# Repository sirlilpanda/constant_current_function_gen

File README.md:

# kicad project constant_current_function_gen

a cool table showing the workflow of all the kicad projects.
| project_name | DRC | ERC |
| ------------ | --- | --- |
| current_gen_class_ab | [❌](https://github.com/sirlilpanda/constant_current_function_gen/actions/runs/16821990167/attempts/1#summary-47650711295)| [❌](https://github.com/sirlilpanda/constant_current_function_gen/actions/runs/16821990167/attempts/1#summary-47650711311) | 
| current_gen | [✅](https://github.com/sirlilpanda/constant_current_function_gen/actions/runs/16821990167/attempts/1#summary-47650711297)| [✅](https://github.com/sirlilpanda/constant_current_function_gen/actions/runs/16821990167/attempts/1#summary-47650711362) | 

for a quick guide check [project setup](#project-setup)

This is a simple project template for new kicad projects. This template has some basic setup already completed such as workflows for auto creating all the things you forget when creating a kicad project such as:

| project_name | schematic | bom | bom report | gerbers |
| ------------ | --------- | --- | ---------- | ------- |
| [current_gen_class_ab](https://github.com/sirlilpanda/constant_current_function_gen/tree/main/./Hardware/current_gen_class_ab) | [current_gen_class_ab_schematic.pdf](https://github.com/sirlilpanda/constant_current_function_gen/tree/main/current_gen_class_ab_schematic.pdf) | [current_gen_class_ab_bill_of_materials.csv](https://github.com/sirlilpanda/constant_current_function_gen/tree/main/current_gen_class_ab_bill_of_materials.csv) | [current_gen_class_ab_bom_report.md](https://github.com/sirlilpanda/constant_current_function_gen/tree/main/current_gen_class_ab_bom_report.md) | [current_gen_class_ab_grbr.zip](https://github.com/sirlilpanda/constant_current_function_gen/tree/main/current_gen_class_ab_gerber.zip) |
| [current_gen](https://github.com/sirlilpanda/constant_current_function_gen/tree/main/./Hardware/current_gen) | [current_gen_schematic.pdf](https://github.com/sirlilpanda/constant_current_function_gen/tree/main/current_gen_schematic.pdf) | [current_gen_bill_of_materials.csv](https://github.com/sirlilpanda/constant_current_function_gen/tree/main/current_gen_bill_of_materials.csv) | [current_gen_bom_report.md](https://github.com/sirlilpanda/constant_current_function_gen/tree/main/current_gen_bom_report.md) | [current_gen_grbr.zip](https://github.com/sirlilpanda/constant_current_function_gen/tree/main/current_gen_gerber.zip) |

This workflow will also run the design rules check on the PCB and schematic to ensure that you upload a working PCB. These reports are uploaded as summaries within the github [actions tab](https://github.com/sirlilpanda/constant_current_function_gen/actions/runs/16821990167). This template has a simple schematic PCB in it (because DRC fails on an empty PCB). Shown below is the example PCB.

besides from that the project also has:

- common predefined trace widths
- smallest vias size [JLCPBC allows](https://jlcpcb.com/capabilities/Capabilities#Drilling)
- custom net colours in the schematic editor
    - `red` for +V
    - `blue` for -V
    - `grey` for ground

to create a repo from this template follow this [guide](https://docs.github.com/en/repositories/creating-and-managing-repositories/creating-a-repository-from-a-template)

contained in this template are:
---
- `.github/` : all files relating to github actions and other admin see [here](https://docs.github.com/en/communities/setting-up-your-project-for-healthy-contributions) for more example of what can be placed in it
    - `report_processing` : where the python scripts are stored for processing the json report data from kicad
    - `report_templates` : where the template for said reports are stored
    - `workflows/` : this is where the github actions are kept
        - `main.yaml` : the main github action that will auto generate all files required and run DRC and ERC
    - `rename.py` : the script for renaming the project
- `hardware/` : this is where the kicad projects live note this can be changed
- `docs/` : this is where the generate docs are placed by default
    - `BOM/`     : where the bill of materials and price breakdown are kept
        - `bill_of_materials.csv`: the auto generated bom for the kicad project
        - `bom_report.md` : a report for the bill of materials
    - `template_schematic.pdf` : the schematic for the kicad project, auto generated by the github action
- `pcbs/` : this is where the auto generated gerbers for the kicad project are stored

- `res/` : where resources are stored for the README

- `.gitignore`: a slightly modified gitignore from the [standard one](https://github.com/github/gitignore/blob/main/KiCad.gitignore)

- `project_settings.yaml` : where the settings for this project is stored

- `README.md` : this file, suggest you change this one creating your project

## project settings
there are currently very few project settings that can be changed (will will be change in the future) these are:
| setting                     | description                                                       |
| --------------------------- | ----------------------------------------------------------------- |
| has_been_set_up             | a flag to tell the setup action if the project has been set up    |
| project_name                | the name of the project, this will be set to the name of the repo |
| production_formats          | the output production format for the PCBs                         |
| dynamic_read_me             | allow the readme to be updated using the given template           |
| bom_template_path           | the template used to write the bom report files                   |
| erc_report_template_path    | the template used to write the erc report files                   |
| drc_report_template_path    | the template used to write the drc report files                   |
| readme_template_path        | the template used to write projects readme                        |
| schematic_output_name       | the name suffix of the generated schematics                       |
| bom_csv_output_name         | the name suffix of the generated bom csv file                     |
| bom_report_output_name      | the name suffix of the generated bom report                       |
| production_file_output_name | the name suffix of the generated production file                  |
| schematic_output_path       | the output path of the generated schematics files                 |
| bom_csv_output_path         | the output path of the generated bom csv file                     |
| bom_report_output_path      | the output path of the generated bom report                       |
| production_file_output_path | the output path of the generated production file                  |

## project setup

### creating a new repo with the template

creating a new template from a repo is simple:

1. click on the button in the top right hand corner called `use this template`

2. when the drop down menu appears click on `create a new repository`

3. once you click you will be brought to this page, note that the repo name you choose here will be the name that you kicad project is called.

after these steps you then need to configure the repo settings to do their magic see [configuring repo settings](#configuring-repo-settings) for what to do next.

### configuring repo settings

once you have created a new repo with the template, you ill have to configure the github action settings. this is because you will get an error that looks something along these lines:

where the action can not commit the changes due to not having permissions follow these steps:
1. open the repo setting

2. then head in to actions : General

3. then scroll down to workflow permissions and ensure that both
    `Read and write permissions` and `Allow GitHub Actions to create and approve pull requests` are ticked as seen below

this should fix the problem if not, go harass stack overflow they need it
Once all of these steps have been followed the workflow should be passing, however the `README.md` will only update on the next push request.

## editing the readme

As this repo can and will automatically update the repo corresponding to the given readme template. If you dont want to use this you can always disable this by setting the `dynamic_read_me` to `false`. but if you want some very cool features like auto updating tables to show what projects are passing the rules check or simple links to parts of your directory. then have a look at the template readme and learn [mustache](https://mustache.github.io/)

## improvements

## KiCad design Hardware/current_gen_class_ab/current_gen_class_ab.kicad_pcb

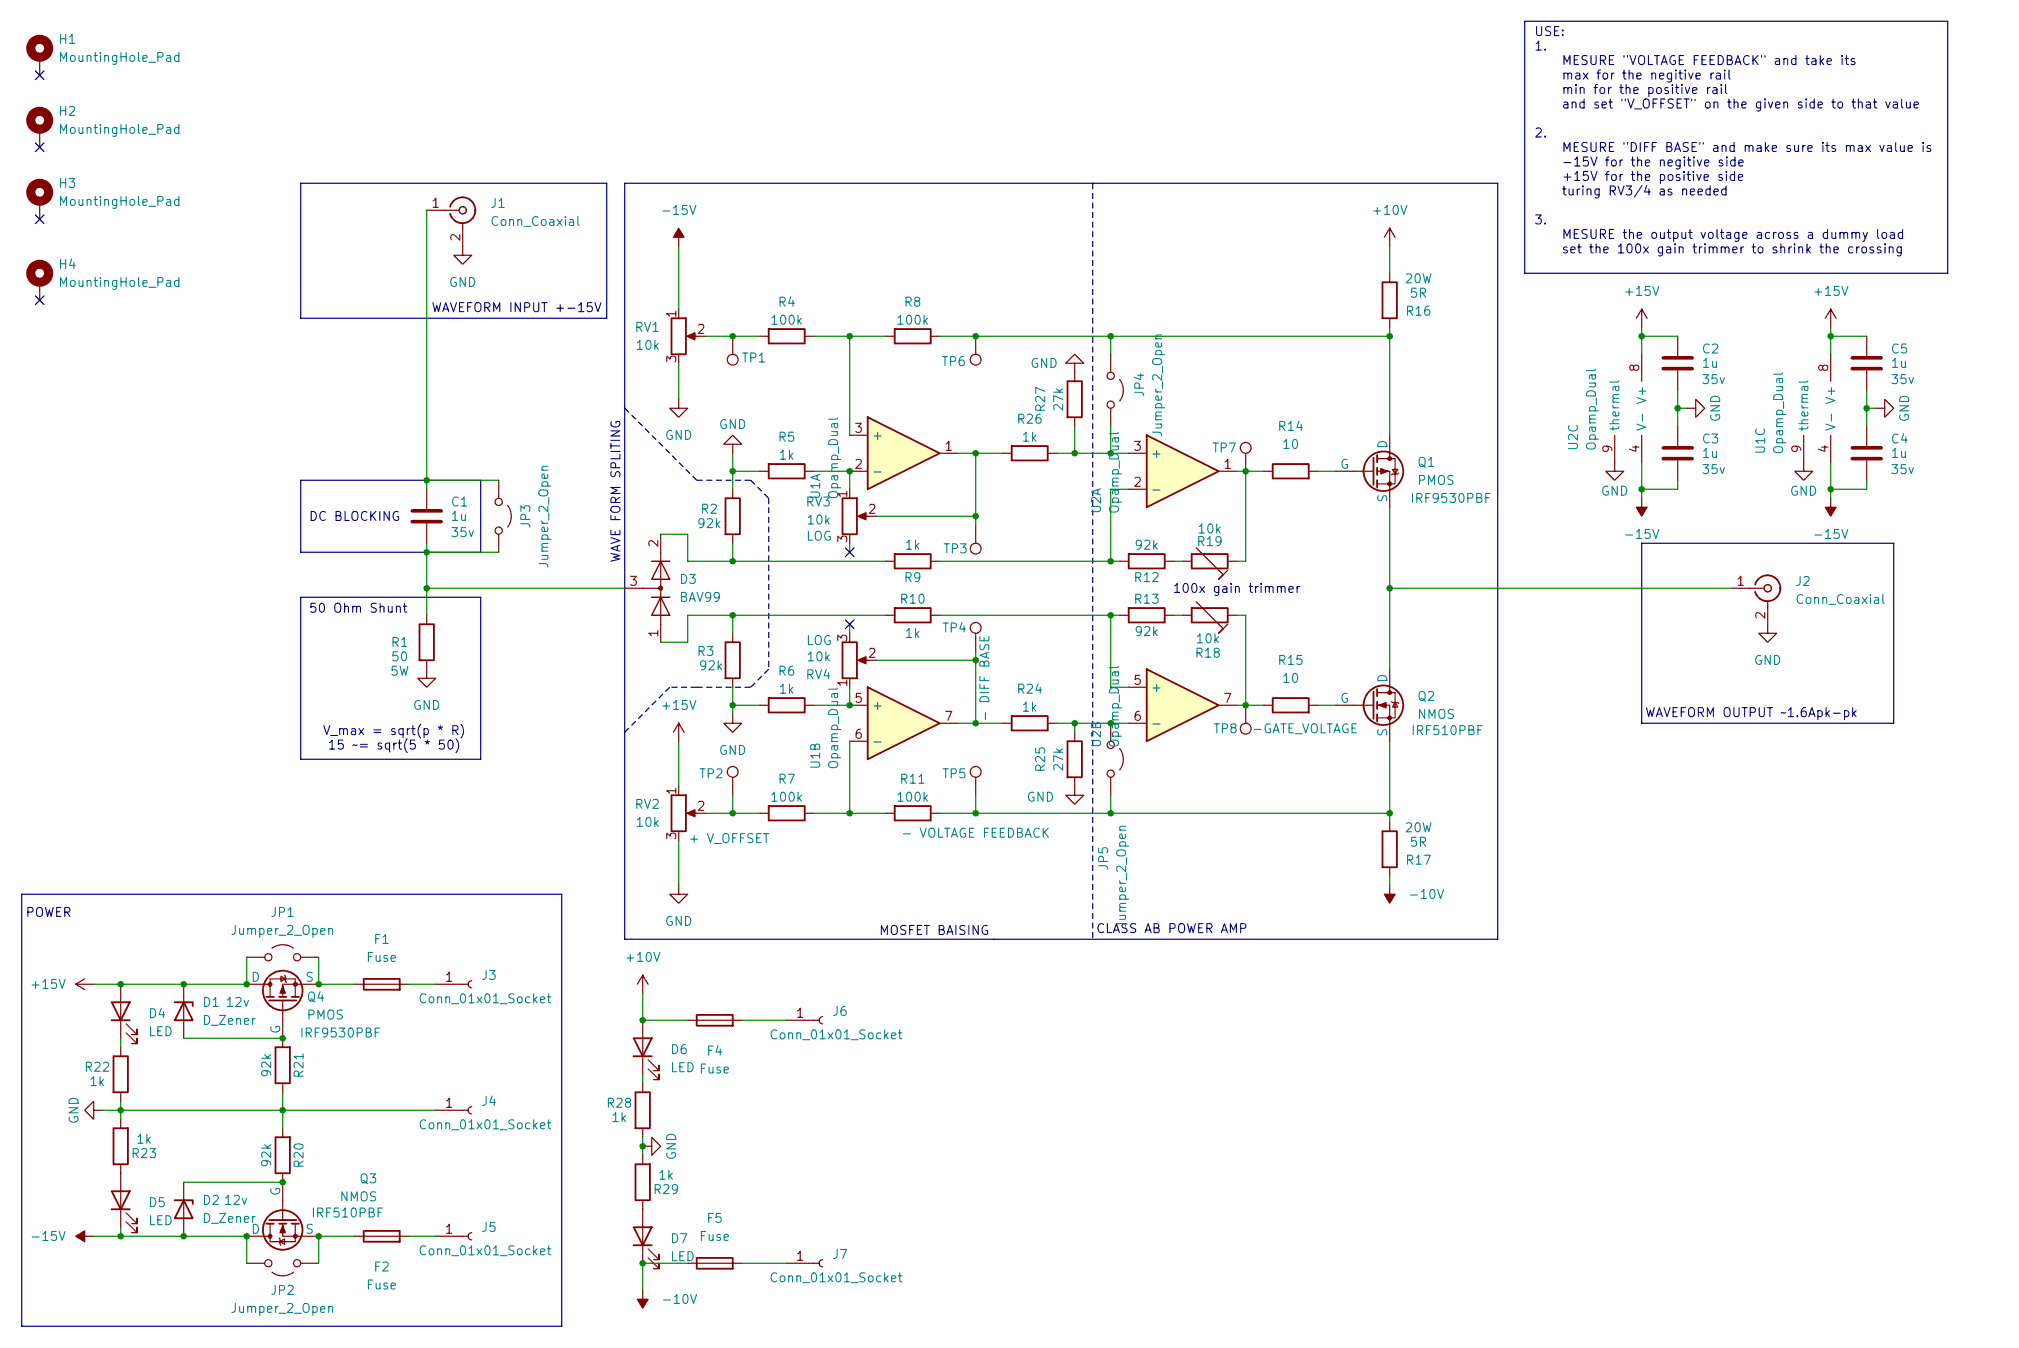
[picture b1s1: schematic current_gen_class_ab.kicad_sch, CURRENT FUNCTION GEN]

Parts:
C1, C2, C3, C4, C5: 1u; C_0805_2012Metric
D1, D2: D_Zener; D_SOD-123
D3: BAV99; SOT-23; Manufactor Part Number BAV99
D4, D5, D6, D7: LED; D_0603_1608Metric
F1, F2, F4, F5: Fuse; Fuseholder_Clip-5x20mm_Bel_FC-203-22_Lateral_P17.80x5.00mm_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
H1, H2, H3, H4: MountingHole_Pad; MountingHole_3.2mm_M3_DIN965_Pad
J1, J2: Conn_Coaxial; BNC_TEConnectivity_1478035_Horizontal
J3, J4, J5, J6, J7: Conn_01x01_Socket; Banana_Jack_1Pin
JP1, JP2, JP3, JP4, JP5: Jumper_2_Open; SolderJumper-2_P1.3mm_Open_TrianglePad1.0x1.5mm
Q1, Q4: PMOS; TO-220-3_Horizontal_TabDown
Q2, Q3: NMOS; TO-220-3_Horizontal_TabDown
R1: 50; R_Axial_DIN0309_L9.0mm_D3.2mm_P12.70mm_Horizontal
R2, R3, R12, R13, R20, R21: 92k; R_0603_1608Metric
R4, R7, R8, R11: 100k; R_0603_1608Metric
R5, R6, R9, R10, R22, R23, R24, R26, R28, R29: 1k; R_0603_1608Metric
R14, R15: 10; R_0603_1608Metric
R16, R17: 5R; TO-220-2_Horizontal_TabDown
R18, R19: 10k; Potentiometer_Bourns_3296W_Vertical
R25, R27: 27k; R_0603_1608Metric
RV1, RV2: 10k; POT_P120PK-x25_TTE
RV3, RV4: 10k; Potentiometer_Bourns_PTV09A-1_Single_Vertical
TP1, TP2, TP3, TP4, TP5, TP6, TP7, TP8: TestPoint; TestPoint_Bridge_Pitch2.54mm_Drill1.3mm
U1, U2: Opamp_Dual; SOIC-8-1EP_3.9x4.9mm_P1.27mm_EP2.29x3mm_ThermalVias

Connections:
+10V: D6.2 (A), F4.1, R16.1
+15V: C2.2, C5.2, D1.1 (K), D4.2 (A), JP1.1 (A), Q4.1 (D), RV2.1, U1.8 (V+), U2.8 (V+)
-10V: D7.1 (K), F5.1, R17.2
-15V: C3.1, C4.1, D2.2 (A), D5.1 (K), JP2.2 (B), Q3.1 (D), RV1.1, U1.4 (V-), U2.4 (V-)
GND: C2.1, C3.2, C4.2, C5.1, J1.2 (Ext), J2.2 (Ext), J4.1, R1.2, R2.1, R3.2, R5.2, R6.2, R20.2, R21.1, R22.2, R23.2, R25.2, R27.1, R28.2, R29.2, RV1.3, RV2.3, U1.9 (thermal), U2.9 (thermal)
unnamed: D1.2 (A), Q4.2 (G), R21.2
unnamed: D2.1 (K), Q3.2 (G), R20.1
unnamed: D3.2 (A), R2.2, R9.2
unnamed: D3.1 (K), R3.1, R10.2
unnamed: D4.1 (K), R22.1
unnamed: D5.2 (A), R23.1
unnamed: D6.1 (K), R28.1
unnamed: D7.2 (A), R29.1
unnamed: C1.2, J1.1 (In), JP3.1 (A)
unnamed: J2.1 (In), Q1.3 (S), Q2.1 (D)
unnamed: F1.2, J3.1
unnamed: F2.2, J5.1
unnamed: F4.2, J6.1
unnamed: F5.2, J7.1
unnamed: F1.1, JP1.2 (B), Q4.3 (S)
unnamed: F2.1, JP2.1 (A), Q3.3 (S)
unnamed: C1.1, D3.3 (K), JP3.2 (B), R1.1
unnamed: JP4.1 (A), Q1.1 (D), R8.1, R16.2, TP6.1
unnamed: JP4.2 (B), R26.1, R27.2, U2.3 (+)
unnamed: JP5.1 (A), R24.1, R25.1, U2.6 (-)
unnamed: JP5.2 (B), Q2.3 (S), R11.1, R17.1, TP5.1
unnamed: Q1.2 (G), R14.2
unnamed: Q2.2 (G), R15.2
unnamed: R4.2, RV1.2, TP1.1
unnamed: R7.2, RV2.2, TP2.1
unnamed: R12.1, R19.2
unnamed: R13.1, R18.2
unnamed: R14.1, R19.1, TP7.1, U2.1
unnamed: R15.1, R18.1, TP8.1, U2.7
unnamed: R24.2, RV4.2, TP4.1, U1.7
unnamed: R26.2, RV3.2, TP3.1, U1.1
unnamed: R4.1, R8.2, U1.3 (+)
unnamed: R5.1, RV3.1, U1.2 (-)
unnamed: R6.1, RV4.1, U1.5 (+)
unnamed: R7.1, R11.2, U1.6 (-)
unnamed: R9.1, R12.2, U2.2 (-)
unnamed: R10.1, R13.2, U2.5 (+)

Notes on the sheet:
MOSFET BAISING
WAVE FORM SPLITING
POWER
V_max = sqrt(p * R) 15 ~= sqrt(5 * 50)
WAVEFORM OUTPUT ~1.6Apk-pk
CLASS AB POWER AMP
100x gain trimmer
50 Ohm Shunt
DC BLOCKING
USE: 1. MESURE "VOLTAGE FEEDBACK" and take its max for the negitive rail min for the positive rail and set "V_OFFSET" on the given side to that value 2. MESURE "DIFF BASE" and make sure its max value is -15V for the negitive side +15V for the positive side turing RV3/4 as needed 3. MESURE the outpu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
WAVEFORM INPUT +-15V

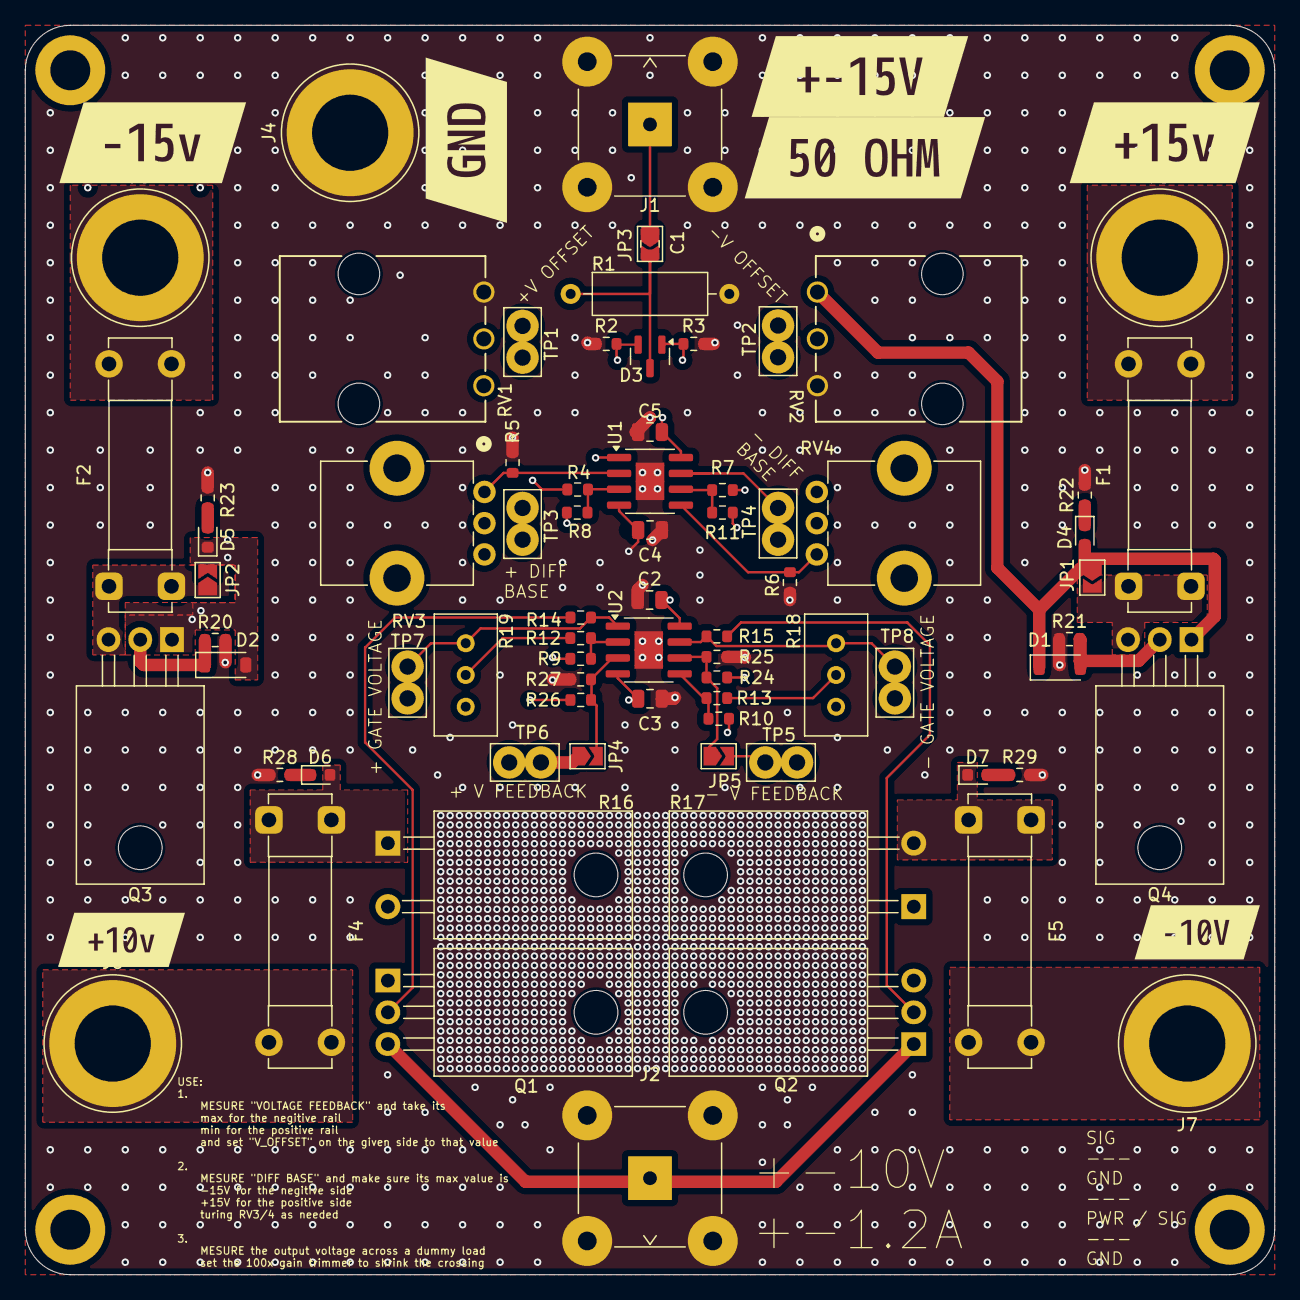
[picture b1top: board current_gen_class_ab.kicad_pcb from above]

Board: 4 copper layers, 100.0 x 100.0 mm, 86 parts (0 on the bottom side), 42 nets.

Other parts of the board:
kibuzzard-68929C8D: G***; kibuzzard-68929C8D
kibuzzard-68929C33: G***; kibuzzard-68929C33
kibuzzard-68929C42: G***; kibuzzard-68929C42
kibuzzard-68929C79: G***; kibuzzard-68929C79
kibuzzard-68929C81: G***; kibuzzard-68929C81
kibuzzard-68929CA4: G***; kibuzzard-68929CA4
kibuzzard-68929CB0: G***; kibuzzard-68929CB0

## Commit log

2025-07-01 init
2025-07-02 production files
2025-07-06 added sch
2025-07-06 added shunt and rpv
2025-07-07 added some docs
2025-07-16 new current gen design
2025-07-22 started to add parts
2025-07-22 added parts for resitors and opamps
2025-07-23 added rvp
2025-07-23 bump
2025-08-03 routed main amp
2025-08-03 swapped pins around to suit pcb better
2025-08-05 routed power started adding stitching and thermal vias
2025-08-05 updated 50ohm shunt
2025-08-06 stitch and slikscreened
2025-08-08 added more to BOM
2025-08-08 updated fill zones and fixed some routing
2025-08-10 added REV A of pcb
